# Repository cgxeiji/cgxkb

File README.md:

# cgxkb
Build guides and schematics of the CGx Keyboard series.

## Keyboards

- [The Space Between You and Me](./tsbym)

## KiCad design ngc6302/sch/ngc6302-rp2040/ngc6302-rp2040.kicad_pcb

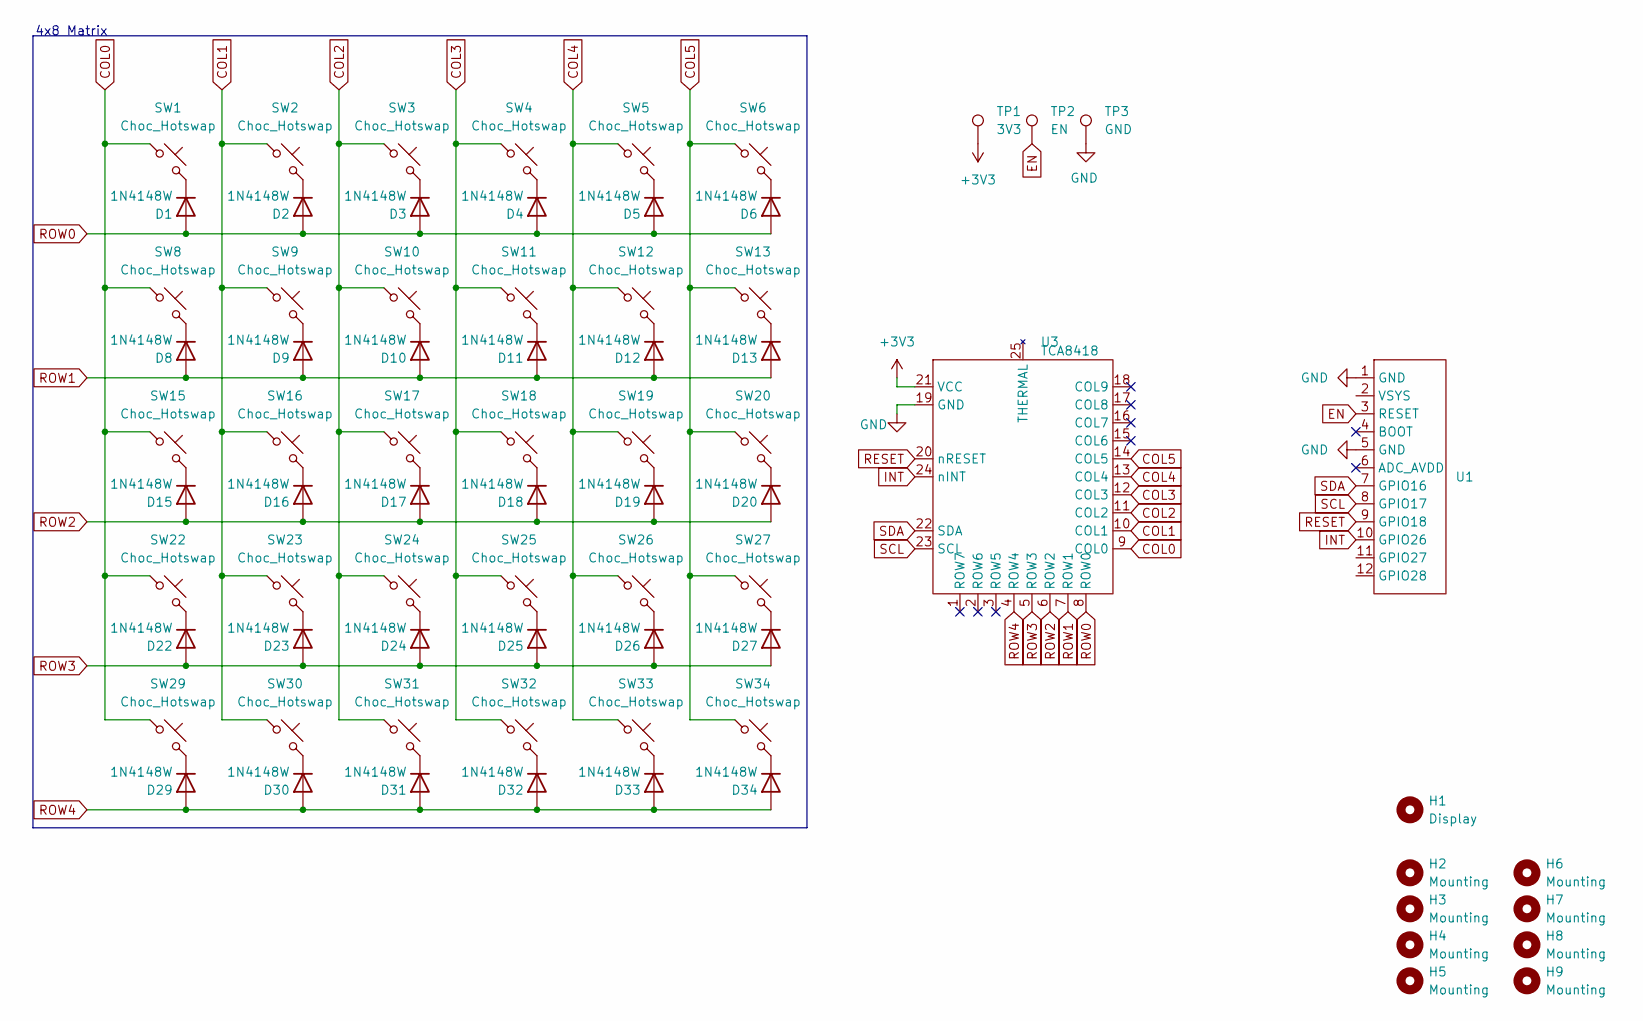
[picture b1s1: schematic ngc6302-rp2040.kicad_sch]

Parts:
D1, D2, D3, D4, D5, D6, D8, D9, D10, D11, D12, D13, D15, D16, D17, D18, D19, D20, D22, D23, D24, D25, D26, D27, D29, D30, D31, D32, D33, D34: 1N4148W; D_SOD-123
H1: Display; Waveshare_Touch_RP2040
H2, H3, H4, H5, H6, H7, H8, H9: Mounting; MountingHole_2.2mm_M2
SW1, SW2, SW3, SW4, SW5, SW6, SW8, SW9, SW10, SW11, SW12, SW13, SW15, SW16, SW17, SW18, SW19, SW20, SW22, SW23, SW24, SW25, SW26, SW27, SW29, SW30, SW31, SW32, SW33, SW34: Choc_Hotswap; SW_Hotswap_Kailh_Choc_V1V2_Plated_1.00u
TP1: 3V3; TestPoint_Pad_D2.5mm
TP2: EN; TestPoint_Pad_D2.5mm
TP3: GND; TestPoint_Pad_2.5x2.5mm
U1: PinHeader_1x12_P2.54mm_Horizontal
U3: TCA8418; WQFN-24-1EP_4x4mm_P0.5mm_EP2.45x2.45mm_ThermalVias

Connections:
+3V3: TP1.1, U3.21 (VCC)
COL0: SW1.1, SW8.1, SW15.1, SW22.1, SW29.1, U3.9 (COL0)
COL1: SW2.1, SW9.1, SW16.1, SW23.1, SW30.1, U3.10 (COL1)
COL2: SW3.1, SW10.1, SW17.1, SW24.1, SW31.1, U3.11 (COL2)
COL3: SW4.1, SW11.1, SW18.1, SW25.1, SW32.1, U3.12 (COL3)
COL4: SW5.1, SW12.1, SW19.1, SW26.1, SW33.1, U3.13 (COL4)
COL5: SW6.1, SW13.1, SW20.1, SW27.1, SW34.1, U3.14 (COL5)
EN: TP2.1, U1.3 (RESET)
GND: TP3.1, U1.1 (GND), U1.5 (GND), U3.19 (GND)
INT: U1.10 (GPIO26), U3.24 (nINT)
unnamed: D1.1 (K), SW1.2
unnamed: D2.1 (K), SW2.2
unnamed: D3.1 (K), SW3.2
unnamed: D4.1 (K), SW4.2
unnamed: D5.1 (K), SW5.2
unnamed: D6.1 (K), SW6.2
unnamed: D8.1 (K), SW8.2
unnamed: D9.1 (K), SW9.2
unnamed: D10.1 (K), SW10.2
unnamed: D11.1 (K), SW11.2
unnamed: D12.1 (K), SW12.2
unnamed: D13.1 (K), SW13.2
unnamed: D15.1 (K), SW15.2
unnamed: D16.1 (K), SW16.2
unnamed: D17.1 (K), SW17.2
unnamed: D18.1 (K), SW18.2
unnamed: D19.1 (K), SW19.2
unnamed: D20.1 (K), SW20.2
unnamed: D22.1 (K), SW22.2
unnamed: D23.1 (K), SW23.2
unnamed: D24.1 (K), SW24.2
unnamed: D25.1 (K), SW25.2
unnamed: D26.1 (K), SW26.2
unnamed: D27.1 (K), SW27.2
unnamed: D29.1 (K), SW29.2
unnamed: D30.1 (K), SW30.2
unnamed: D31.1 (K), SW31.2
unnamed: D32.1 (K), SW32.2
unnamed: D33.1 (K), SW33.2
unnamed: D34.1 (K), SW34.2
RESET: U1.9 (GPIO18), U3.20 (nRESET)
ROW0: D1.2 (A), D2.2 (A), D3.2 (A), D4.2 (A), D5.2 (A), D6.2 (A), U3.8 (ROW0)
ROW1: D8.2 (A), D9.2 (A), D10.2 (A), D11.2 (A), D12.2 (A), D13.2 (A), U3.7 (ROW1)
ROW2: D15.2 (A), D16.2 (A), D17.2 (A), D18.2 (A), D19.2 (A), D20.2 (A), U3.6 (ROW2)
ROW3: D22.2 (A), D23.2 (A), D24.2 (A), D25.2 (A), D26.2 (A), D27.2 (A), U3.5 (ROW3)
ROW4: D29.2 (A), D30.2 (A), D31.2 (A), D32.2 (A), D33.2 (A), D34.2 (A), U3.4 (ROW4)
SCL: U1.8 (GPIO17), U3.23 (SCL)
SDA: U1.7 (GPIO16), U3.22 (SDA)

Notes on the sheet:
4x8 Matrix

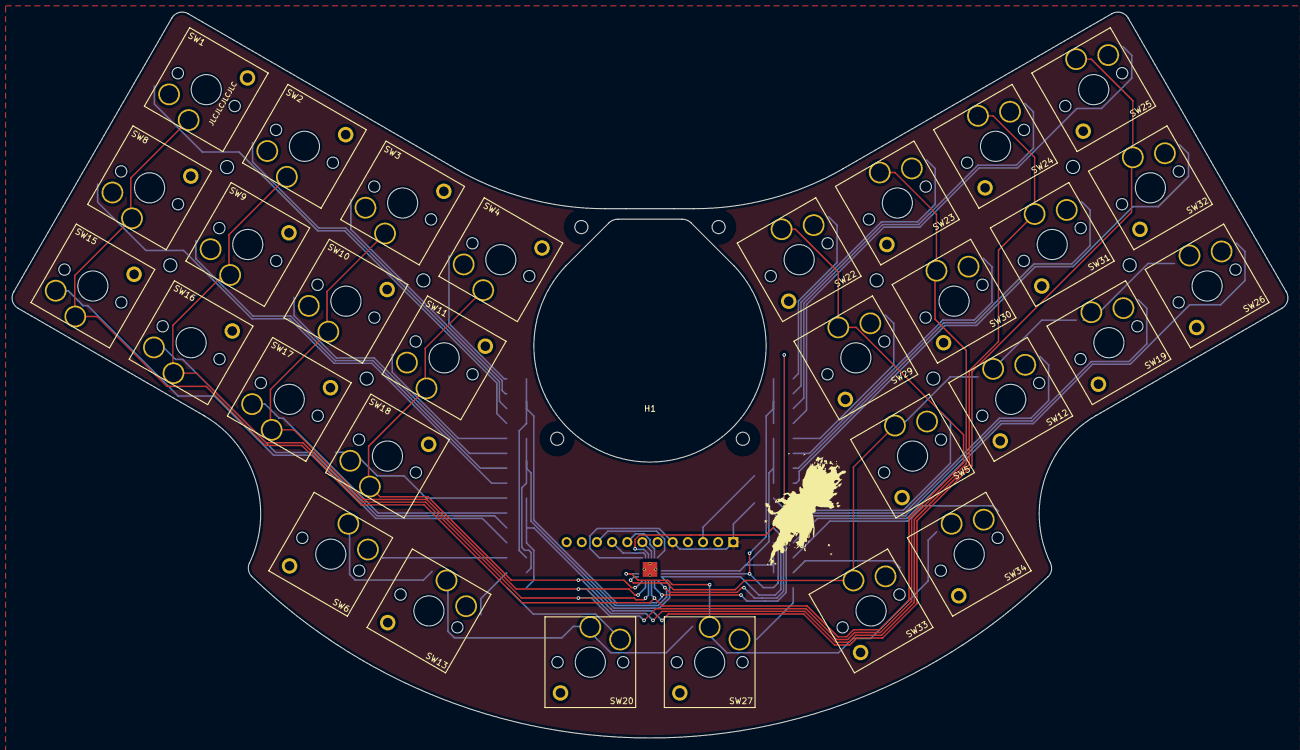
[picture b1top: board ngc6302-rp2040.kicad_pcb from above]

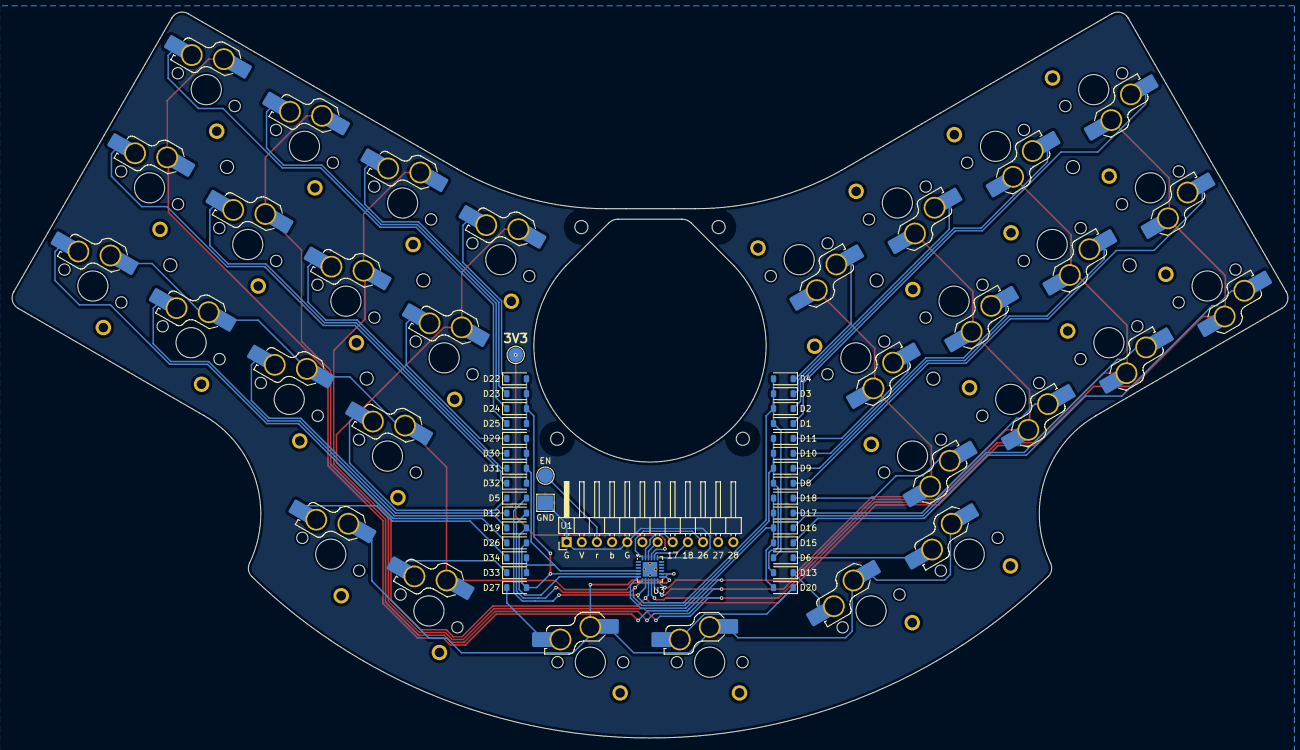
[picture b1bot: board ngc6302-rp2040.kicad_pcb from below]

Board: 2 copper layers, 213.8 x 121.7 mm, 74 parts (35 on the bottom side), 48 nets.

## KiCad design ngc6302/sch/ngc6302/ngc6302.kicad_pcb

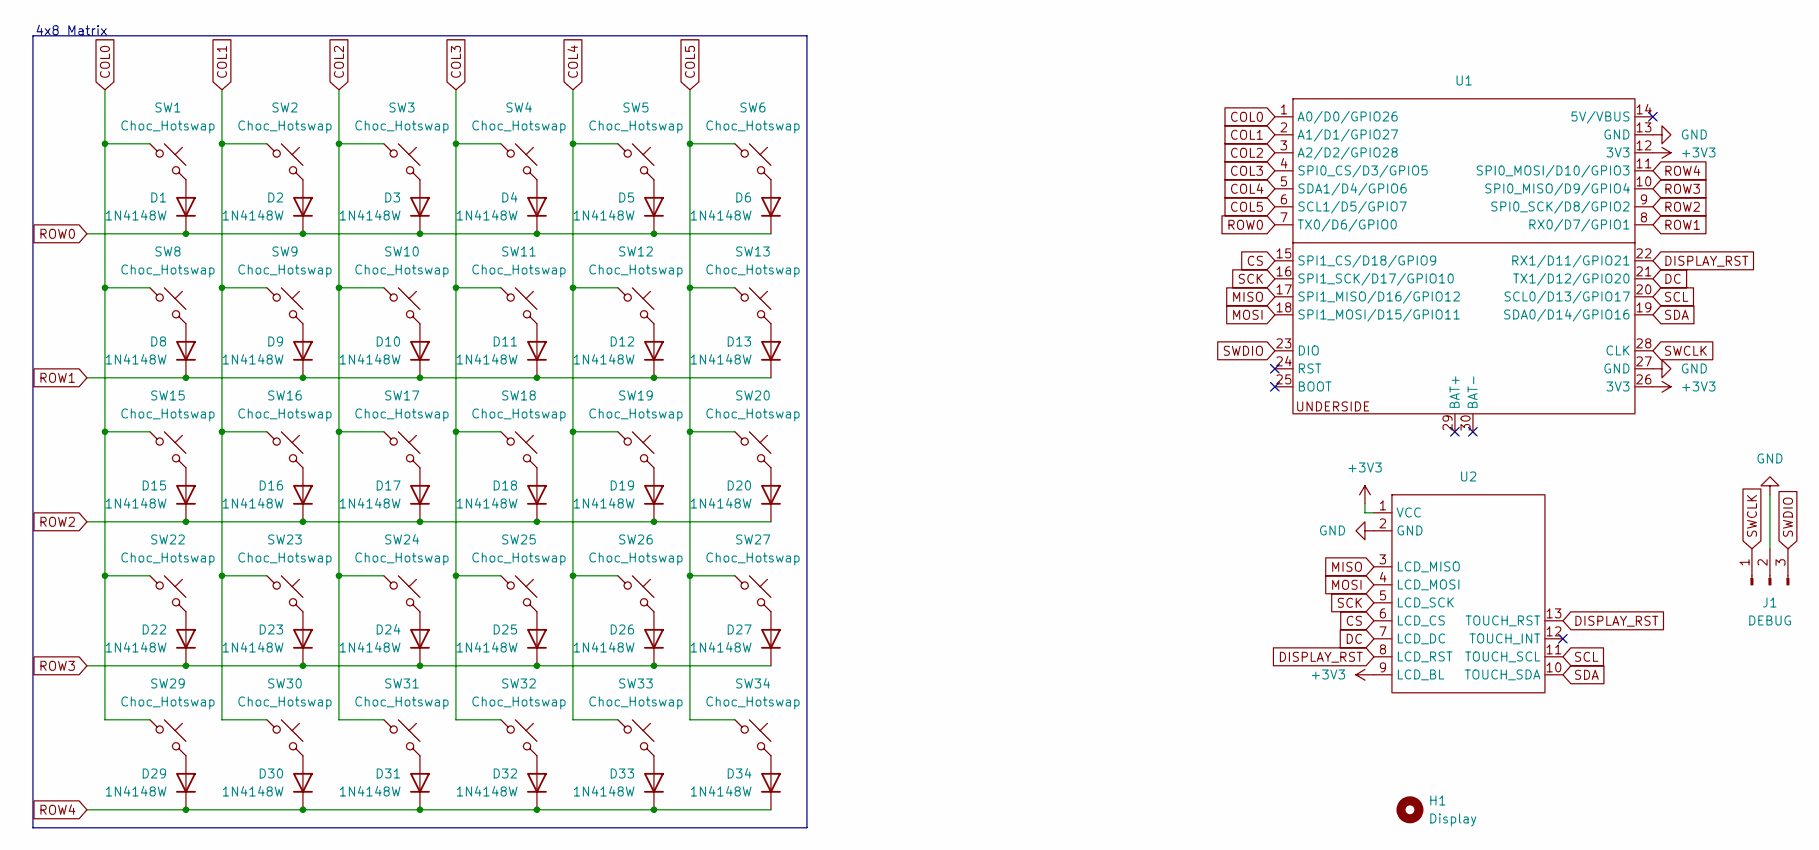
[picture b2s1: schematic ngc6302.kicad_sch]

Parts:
D1, D2, D3, D4, D5, D6, D8, D9, D10, D11, D12, D13, D15, D16, D17, D18, D19, D20, D22, D23, D24, D25, D26, D27, D29, D30, D31, D32, D33, D34: 1N4148W; D_SOD-123
H1: Display; Waveshare_Touch_LCD_Round
J1: DEBUG
SW1, SW2, SW3, SW4, SW5, SW6, SW8, SW9, SW10, SW11, SW12, SW13, SW15, SW16, SW17, SW18, SW19, SW20, SW22, SW23, SW24, SW25, SW26, SW27, SW29, SW30, SW31, SW32, SW33, SW34: Choc_Hotswap; SW_Hotswap_Kailh_Choc_V1V2_Plated_1.00u
U1: XIAO_2350
U2: PinHeader_1x13_P2.54mm_Horizontal

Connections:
+3V3: U1.12 (3V3), U1.26 (3V3), U2.1 (VCC), U2.9 (LCD_BL)
COL0: SW1.1, SW8.1, SW15.1, SW22.1, SW29.1, U1.1 (A0/D0/GPIO26)
COL1: SW2.1, SW9.1, SW16.1, SW23.1, SW30.1, U1.2 (A1/D1/GPIO27)
COL2: SW3.1, SW10.1, SW17.1, SW24.1, SW31.1, U1.3 (A2/D2/GPIO28)
COL3: SW4.1, SW11.1, SW18.1, SW25.1, SW32.1, U1.4 (SPI0_CS/D3/GPIO5)
COL4: SW5.1, SW12.1, SW19.1, SW26.1, SW33.1, U1.5 (SDA1/D4/GPIO6)
COL5: SW6.1, SW13.1, SW20.1, SW27.1, SW34.1, U1.6 (SCL1/D5/GPIO7)
CS: U1.15 (SPI1_CS/D18/GPIO9), U2.6 (LCD_CS)
DC: U1.21 (TX1/D12/GPIO20), U2.7 (LCD_DC)
DISPLAY_RST: U1.22 (RX1/D11/GPIO21), U2.8 (LCD_RST), U2.13 (TOUCH_RST)
GND: J1.2, U1.13 (GND), U1.27 (GND), U2.2 (GND)
MISO: U1.17 (SPI1_MISO/D16/GPIO12), U2.3 (LCD_MISO)
MOSI: U1.18 (SPI1_MOSI/D15/GPIO11), U2.4 (LCD_MOSI)
unnamed: D1.2 (A), SW1.2
unnamed: D2.2 (A), SW2.2
unnamed: D3.2 (A), SW3.2
unnamed: D4.2 (A), SW4.2
unnamed: D5.2 (A), SW5.2
unnamed: D6.2 (A), SW6.2
unnamed: D8.2 (A), SW8.2
unnamed: D9.2 (A), SW9.2
unnamed: D10.2 (A), SW10.2
unnamed: D11.2 (A), SW11.2
unnamed: D12.2 (A), SW12.2
unnamed: D13.2 (A), SW13.2
unnamed: D15.2 (A), SW15.2
unnamed: D16.2 (A), SW16.2
unnamed: D17.2 (A), SW17.2
unnamed: D18.2 (A), SW18.2
unnamed: D19.2 (A), SW19.2
unnamed: D20.2 (A), SW20.2
unnamed: D22.2 (A), SW22.2
unnamed: D23.2 (A), SW23.2
unnamed: D24.2 (A), SW24.2
unnamed: D25.2 (A), SW25.2
unnamed: D26.2 (A), SW26.2
unnamed: D27.2 (A), SW27.2
unnamed: D29.2 (A), SW29.2
unnamed: D30.2 (A), SW30.2
unnamed: D31.2 (A), SW31.2
unnamed: D32.2 (A), SW32.2
unnamed: D33.2 (A), SW33.2
unnamed: D34.2 (A), SW34.2
ROW0: D1.1 (K), D2.1 (K), D3.1 (K), D4.1 (K), D5.1 (K), D6.1 (K), U1.7 (TX0/D6/GPIO0)
ROW1: D8.1 (K), D9.1 (K), D10.1 (K), D11.1 (K), D12.1 (K), D13.1 (K), U1.8 (RX0/D7/GPIO1)
ROW2: D15.1 (K), D16.1 (K), D17.1 (K), D18.1 (K), D19.1 (K), D20.1 (K), U1.9 (SPI0_SCK/D8/GPIO2)
ROW3: D22.1 (K), D23.1 (K), D24.1 (K), D25.1 (K), D26.1 (K), D27.1 (K), U1.10 (SPI0_MISO/D9/GPIO4)
ROW4: D29.1 (K), D30.1 (K), D31.1 (K), D32.1 (K), D33.1 (K), D34.1 (K), U1.11 (SPI0_MOSI/D10/GPIO3)
SCK: U1.16 (SPI1_SCK/D17/GPIO10), U2.5 (LCD_SCK)
SCL: U1.20 (SCL0/D13/GPIO17), U2.11 (TOUCH_SCL)
SDA: U1.19 (SDA0/D14/GPIO16), U2.10 (TOUCH_SDA)
SWCLK: J1.1, U1.28 (CLK)
SWDIO: J1.3, U1.23 (DIO)

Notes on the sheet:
4x8 Matrix

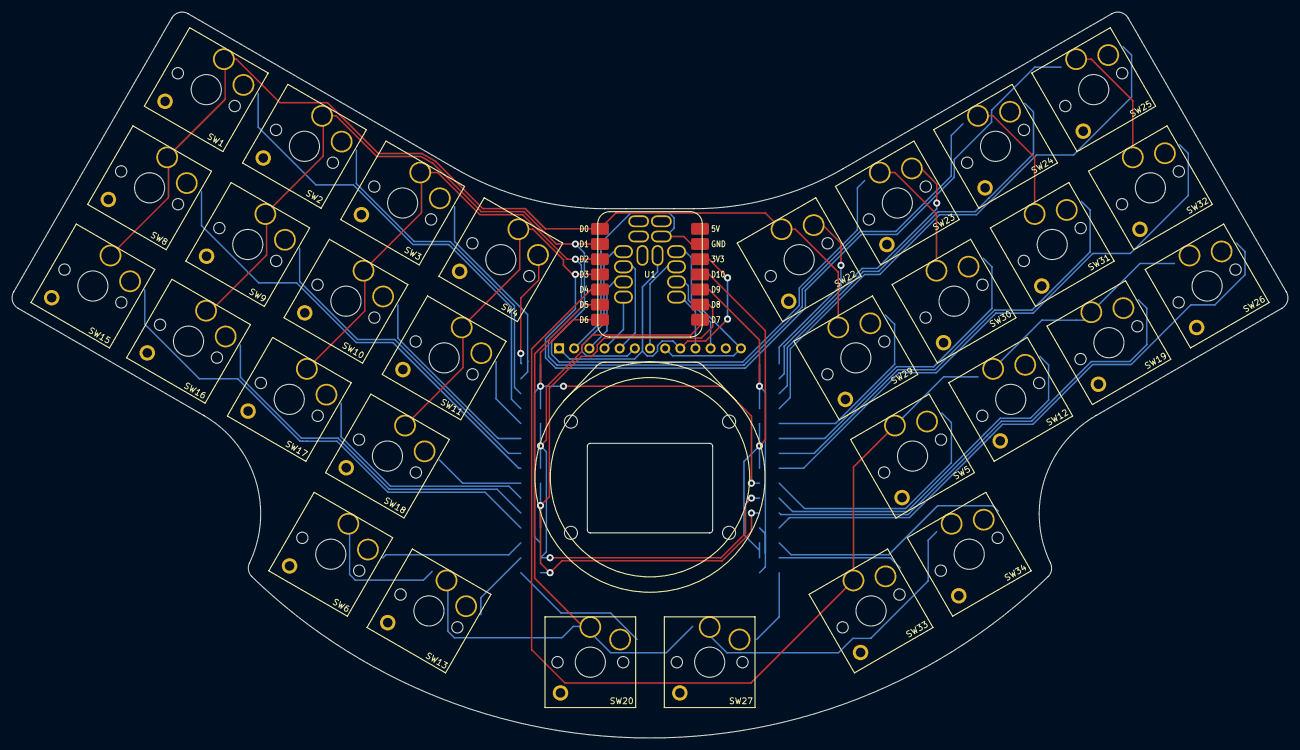
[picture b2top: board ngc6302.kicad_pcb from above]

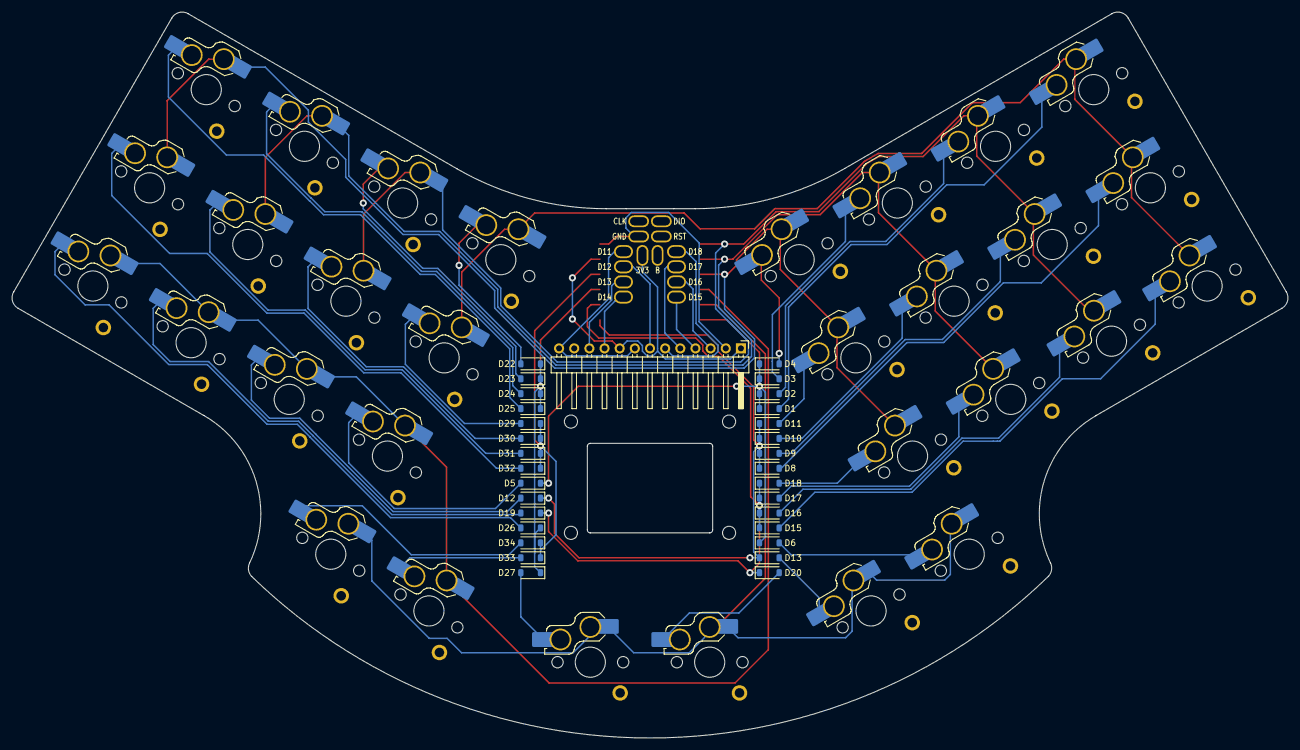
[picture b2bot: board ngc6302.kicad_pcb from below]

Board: 2 copper layers, 213.8 x 121.7 mm, 63 parts (31 on the bottom side), 51 nets.

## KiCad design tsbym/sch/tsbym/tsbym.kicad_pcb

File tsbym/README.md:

# The Space Between You and Me

**The Space Between You and Me** is a split ortholinear 3x5 keyboard with 4
thumb keys, a trackball, and a rotary encoder.

## Build Guide

Check the build guide [here (English)](./build_guide_en.md), if you are
assembling your keyboard from scratch.

## Firmware Guide

Check the firmware guide [here (English)](./firmware_guide_en.md), if you want
to customize your keyboard.

## Schematic

Check the schematic [here](./sch/tsbym/).

## 3D Printed Case

Download the files [here](https://www.printables.com/model/987788-tsbym-case).

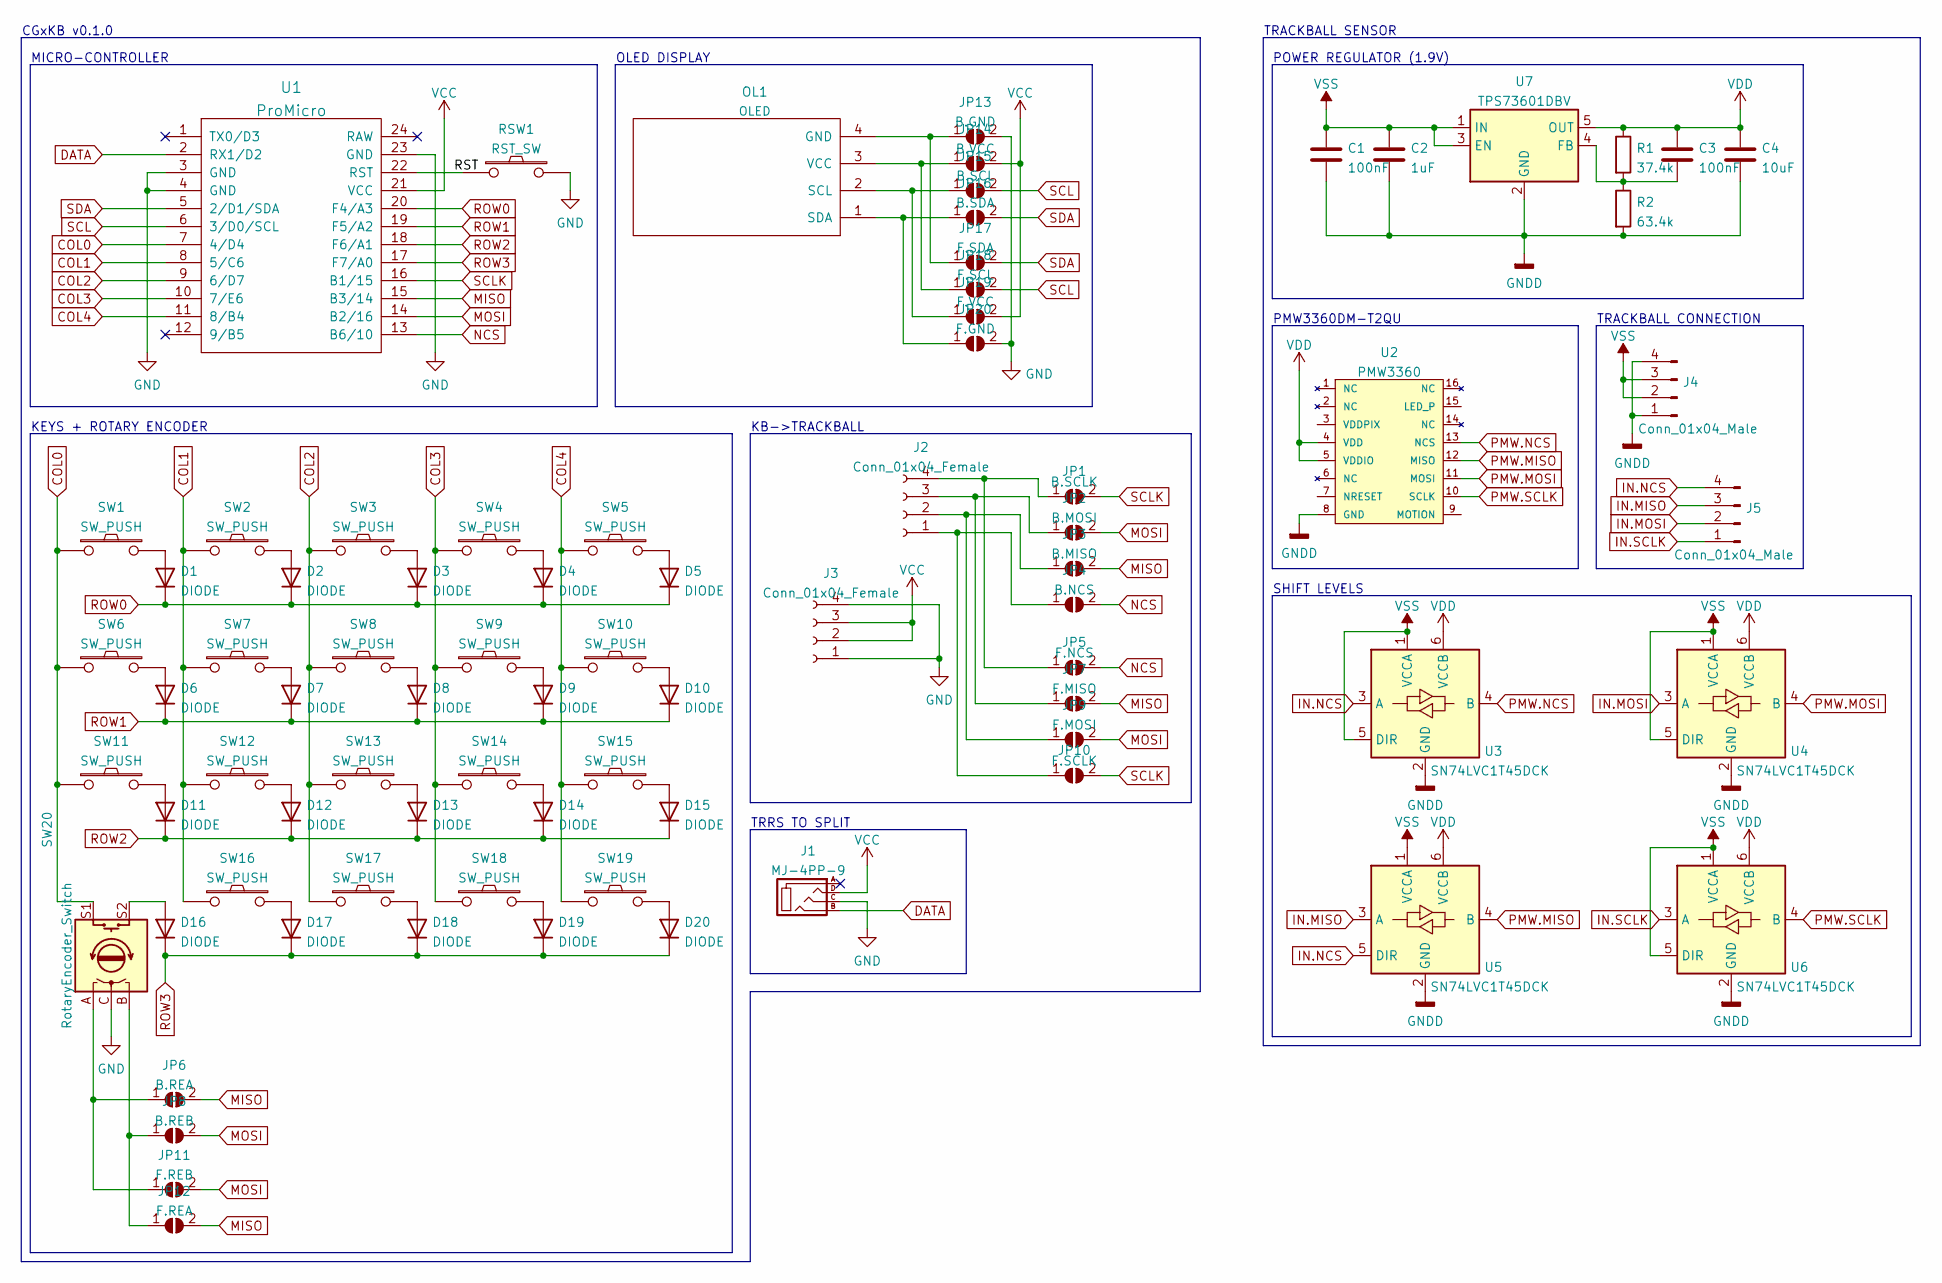
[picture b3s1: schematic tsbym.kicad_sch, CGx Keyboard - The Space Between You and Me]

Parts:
C1, C3: 100nF; C_0402_1005Metric_Pad0.74x0.62mm_HandSolder; LCSC C1525
C2: 1uF; C_0402_1005Metric_Pad0.74x0.62mm_HandSolder; LCSC C52923
C4: 10uF; C_0402_1005Metric_Pad0.74x0.62mm_HandSolder; LCSC C15525
D1, D2, D3, D4, D5, D6, D7, D8, D9, D10, D11, D12, D13, D14, D15, D16, D17, D18, D19, D20: DIODE; D3_TH_SMD
J1: MJ-4PP-9
J2, J3: Conn_01x04_Female; OLED
J4, J5: Conn_01x04_Male; OLED
JP1: B.SCLK; SolderJumper-2_P1.3mm_Open_RoundedPad1.0x1.5mm
JP2: B.MOSI; SolderJumper-2_P1.3mm_Open_RoundedPad1.0x1.5mm
JP3: B.MISO; SolderJumper-2_P1.3mm_Open_RoundedPad1.0x1.5mm
JP4: B.NCS; SolderJumper-2_P1.3mm_Open_RoundedPad1.0x1.5mm
JP5: F.NCS; SolderJumper-2_P1.3mm_Open_RoundedPad1.0x1.5mm
JP6: B.REA; SolderJumper-2_P1.3mm_Open_RoundedPad1.0x1.5mm
JP7: F.MISO; SolderJumper-2_P1.3mm_Open_RoundedPad1.0x1.5mm
JP8: B.REB; SolderJumper-2_P1.3mm_Open_RoundedPad1.0x1.5mm
JP9: F.MOSI; SolderJumper-2_P1.3mm_Open_RoundedPad1.0x1.5mm
JP10: F.SCLK; SolderJumper-2_P1.3mm_Open_RoundedPad1.0x1.5mm
JP11: F.REB; SolderJumper-2_P1.3mm_Open_RoundedPad1.0x1.5mm
JP12: F.REA; SolderJumper-2_P1.3mm_Open_RoundedPad1.0x1.5mm
JP13: B.GND; SolderJumper-2_P1.3mm_Open_RoundedPad1.0x1.5mm
JP14: B.VCC; SolderJumper-2_P1.3mm_Open_RoundedPad1.0x1.5mm
JP15: B.SCL; SolderJumper-2_P1.3mm_Open_RoundedPad1.0x1.5mm
JP16: B.SDA; SolderJumper-2_P1.3mm_Open_RoundedPad1.0x1.5mm
JP17: F.SDA; SolderJumper-2_P1.3mm_Open_RoundedPad1.0x1.5mm
JP18: F.SCL; SolderJumper-2_P1.3mm_Open_RoundedPad1.0x1.5mm
JP19: F.VCC; SolderJumper-2_P1.3mm_Open_RoundedPad1.0x1.5mm
JP20: F.GND; SolderJumper-2_P1.3mm_Open_RoundedPad1.0x1.5mm
OL1: OLED
R1: 37.4k; R_0402_1005Metric_Pad0.72x0.64mm_HandSolder; LCSC C25888
R2: 63.4k; R_0402_1005Metric_Pad0.72x0.64mm_HandSolder; LCSC C38606
RSW1: RST_SW; ResetSW
SW1, SW2, SW3, SW4, SW5, SW6, SW7, SW8, SW9, SW10, SW11, SW12, SW13, SW14, SW15, SW16, SW17, SW18, SW19: SW_PUSH; CherryMX_MidHeight_Choc_Hotswap
SW20: RotaryEncoder_Switch; RotaryEncoder_Alps_EC11E-Switch_Vertical_H20mm
U1: ProMicro; ProMicro_v2
U2: PMW3360; DIP-16_W10.16mm
U3, U4, U5, U6: SN74LVC1T45DCK; SOT-363_SC-70-6; LCSC C9382
U7: TPS73601DBV; SOT-23-5; LCSC C59200

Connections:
/RST: RSW1.1, U1.22 (RST)
COL0: SW1.1, SW6.1, SW11.1, SW20.S1, U1.7 (4/D4)
COL1: SW2.1, SW7.1, SW12.1, SW16.1, U1.8 (5/C6)
COL2: SW3.1, SW8.1, SW13.1, SW17.1, U1.9 (6/D7)
COL3: SW4.1, SW9.1, SW14.1, SW18.1, U1.10 (7/E6)
COL4: SW5.1, SW10.1, SW15.1, SW19.1, U1.11 (8/B4)
DATA: J1.B, U1.2 (RX1/D2)
GND: J1.C, J3.1, J3.4, JP13.2 (B), JP20.2 (B), RSW1.2, SW20.C, U1.3 (GND), U1.4 (GND), U1.23 (GND)
GNDD: C1.2, C2.2, C4.2, J4.1, J4.4, R2.2, U2.8 (GND), U3.2 (GND), U4.2 (GND), U5.2 (GND), U6.2 (GND), U7.2 (GND)
IN.MISO: J5.3, U5.3 (A)
IN.MOSI: J5.2, U4.3 (A)
IN.NCS: J5.4, U3.3 (A), U5.5 (DIR)
IN.SCLK: J5.1, U6.3 (A)
MISO: JP3.2 (B), JP6.2 (B), JP7.2 (B), JP12.2 (B), U1.15 (B3/14)
MOSI: JP2.2 (B), JP8.2 (B), JP9.2 (B), JP11.2 (B), U1.14 (B2/16)
NCS: JP4.2 (B), JP5.2 (B), U1.13 (B6/10)
unnamed: C3.2, R1.2, R2.1, U7.4 (FB)
unnamed: D1.1 (A), SW1.2
unnamed: D2.1 (A), SW2.2
unnamed: D3.1 (A), SW3.2
unnamed: D4.1 (A), SW4.2
unnamed: D5.1 (A), SW5.2
unnamed: D6.1 (A), SW6.2
unnamed: D7.1 (A), SW7.2
unnamed: D8.1 (A), SW8.2
unnamed: D9.1 (A), SW9.2
unnamed: D10.1 (A), SW10.2
unnamed: D11.1 (A), SW11.2
unnamed: D12.1 (A), SW12.2
unnamed: D13.1 (A), SW13.2
unnamed: D14.1 (A), SW14.2
unnamed: D15.1 (A), SW15.2
unnamed: D16.1 (A), SW20.S2
unnamed: D17.1 (A), SW16.2
unnamed: D18.1 (A), SW17.2
unnamed: D19.1 (A), SW18.2
unnamed: D20.1 (A), SW19.2
unnamed: J2.1, JP4.1 (A), JP10.1 (A)
unnamed: J2.2, JP3.1 (A), JP9.1 (A)
unnamed: J2.3, JP2.1 (A), JP7.1 (A)
unnamed: J2.4, JP1.1 (A), JP5.1 (A)
unnamed: JP6.1 (A), JP11.1 (A), SW20.A
unnamed: JP8.1 (A), JP12.1 (A), SW20.B
unnamed: JP13.1 (A), JP17.1 (A), OL1.4 (GND)
unnamed: JP14.1 (A), JP18.1 (A), OL1.3 (VCC)
unnamed: JP15.1 (A), JP19.1 (A), OL1.2 (SCL)
unnamed: JP16.1 (A), JP20.1 (A), OL1.1 (SDA)
PWM.MISO: U2.12 (MISO), U5.4 (B)
PWM.MOSI: U2.11 (MOSI), U4.4 (B)
PWM.NCS: U2.13 (NCS), U3.4 (B)
PWM.SCLK: U2.10 (SCLK), U6.4 (B)
ROW0: D1.2 (K), D2.2 (K), D3.2 (K), D4.2 (K), D5.2 (K), U1.20 (F4/A3)
ROW1: D6.2 (K), D7.2 (K), D8.2 (K), D9.2 (K), D10.2 (K), U1.19 (F5/A2)
ROW2: D11.2 (K), D12.2 (K), D13.2 (K), D14.2 (K), D15.2 (K), U1.18 (F6/A1)
ROW3: D16.2 (K), D17.2 (K), D18.2 (K), D19.2 (K), D20.2 (K), U1.17 (F7/A0)
SCL: JP15.2 (B), JP18.2 (B), U1.6 (3/D0/SCL)
SCLK: JP1.2 (B), JP10.2 (B), U1.16 (B1/15)
SDA: JP16.2 (B), JP17.2 (B), U1.5 (2/D1/SDA)
VCC: J1.D, J3.2, J3.3, JP14.2 (B), JP19.2 (B), U1.21 (VCC)
VDD: C3.1, C4.1, R1.1, U2.4 (VDD), U2.5 (VDDIO), U3.6 (VCCB), U4.6 (VCCB), U5.6 (VCCB), U6.6 (VCCB), U7.5 (OUT)
VSS: C1.1, C2.1, J4.2, J4.3, U3.1 (VCCA), U3.5 (DIR), U4.1 (VCCA), U4.5 (DIR), U5.1 (VCCA), U6.1 (VCCA), U6.5 (DIR), U7.1 (IN), U7.3 (EN)

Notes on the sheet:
CGxKB v0.1.0
MICRO-CONTROLLER
KEYS + ROTARY ENCODER
OLED DISPLAY
KB->TRACKBALL
TRRS TO SPLIT
TRACKBALL SENSOR
POWER REGULATOR (1.9V)
PMW3360DM-T2QU
SHIFT LEVELS
TRACKBALL CONNECTION

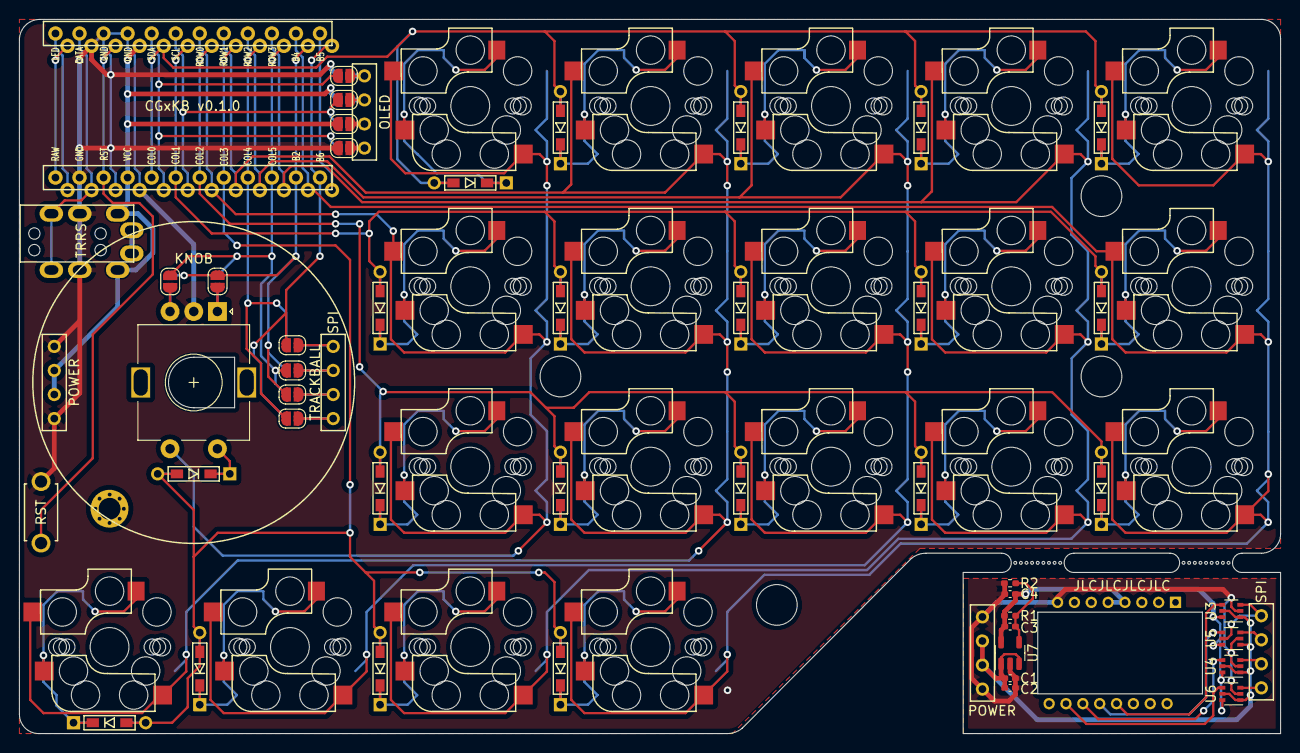
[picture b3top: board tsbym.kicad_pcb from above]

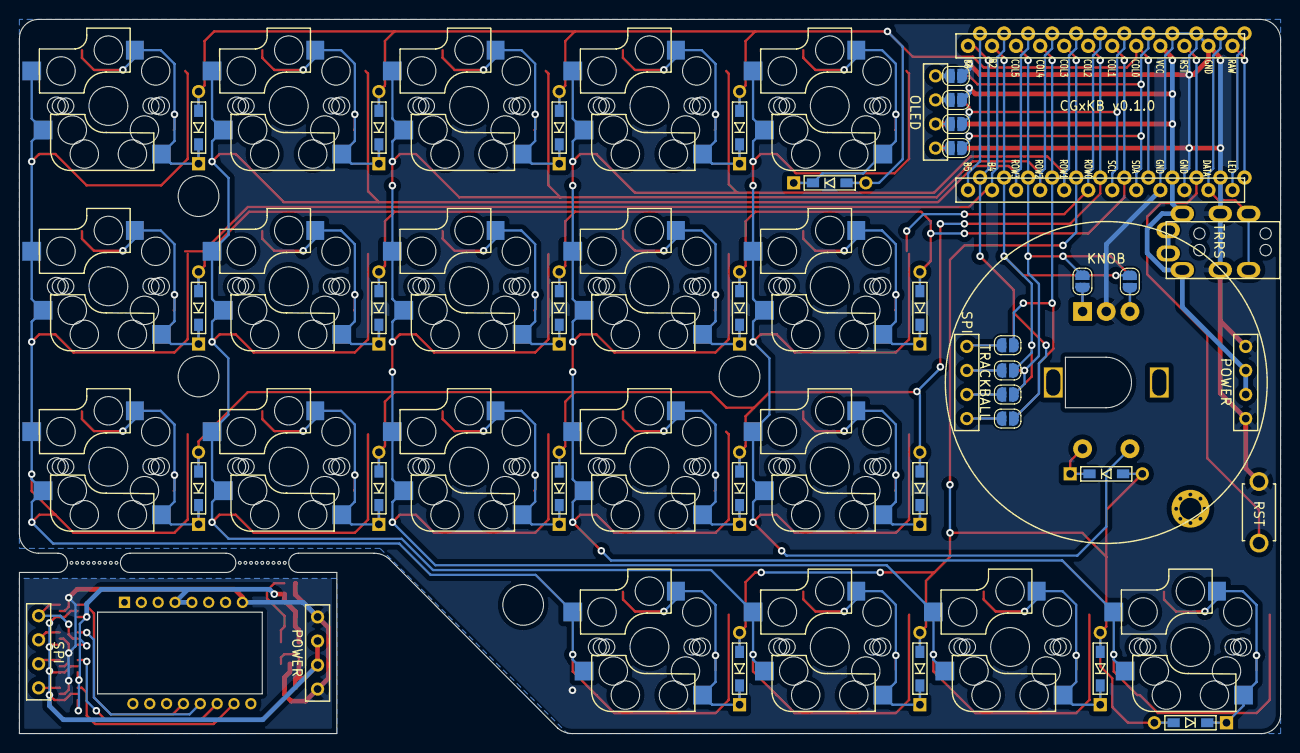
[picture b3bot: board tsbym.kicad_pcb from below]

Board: 2 copper layers, 133.2 x 75.4 mm, 85 parts (10 on the bottom side), 61 nets.

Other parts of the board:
Ref**: Val**; spacer_m2
Ref**#2: Val**; M2_HOLE_v3
Ref**#3, Ref**#4, Ref**#5: Val**; spacer_m2

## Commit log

2021-10-30 Writing guides for The Space Between You and Me.
2021-10-30 Highlighted some pictures.
2021-11-06 Added more to the guide.
2021-11-06 Added alignment information.
2021-11-11 Added firmware guide.
2021-11-11 Updated README. Added boot magic.
2021-11-11 Added index.
2021-11-14 Added schematic
2021-11-14 Updated README.
2021-11-17 Updated build guide with trackball.
2023-02-21 Added Binary Star System.
2023-02-21 Added BOM.
2024-08-19 Uploaded ngc6302
2024-08-27 Added 3D files
